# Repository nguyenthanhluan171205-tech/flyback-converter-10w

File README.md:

# flyback-converter-10w
Design, simulation, PCB layout, and experimental validation of a 10W Flyback converter (80-220VAC to 12VDC, 90% efficiency).

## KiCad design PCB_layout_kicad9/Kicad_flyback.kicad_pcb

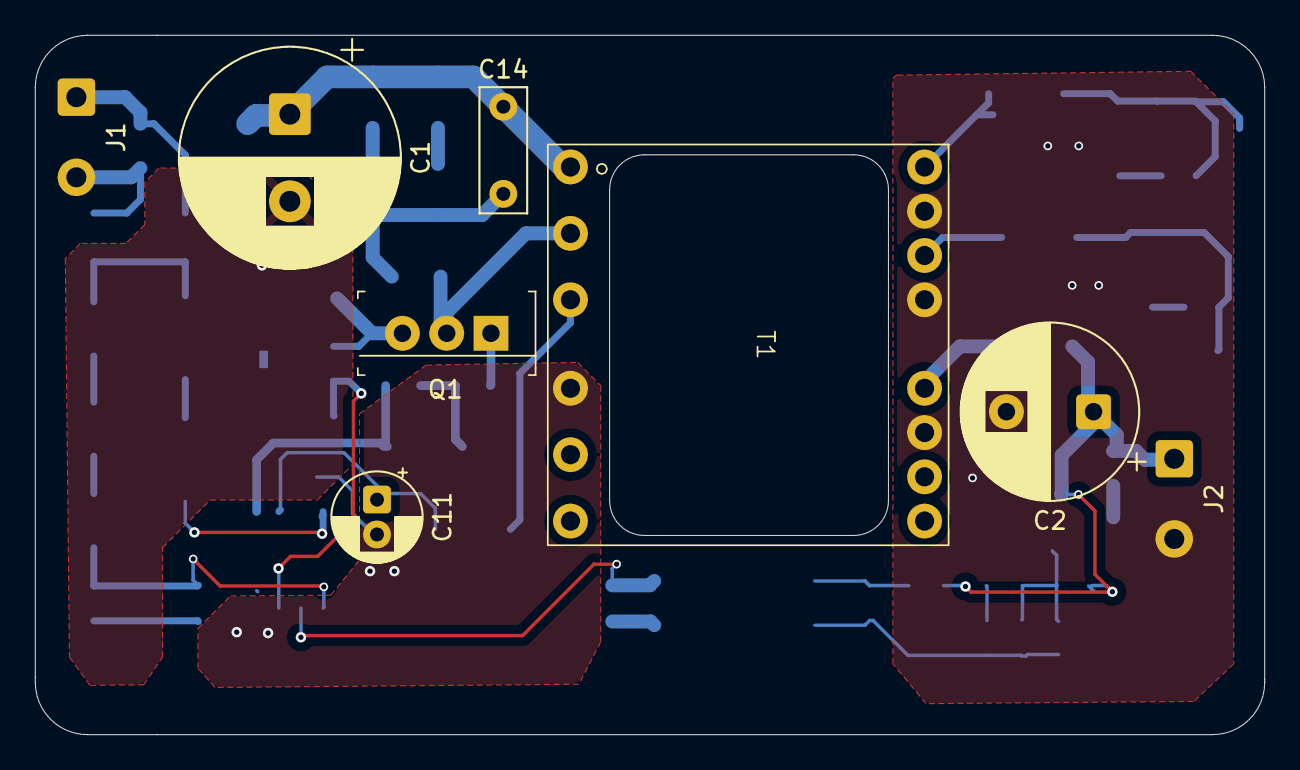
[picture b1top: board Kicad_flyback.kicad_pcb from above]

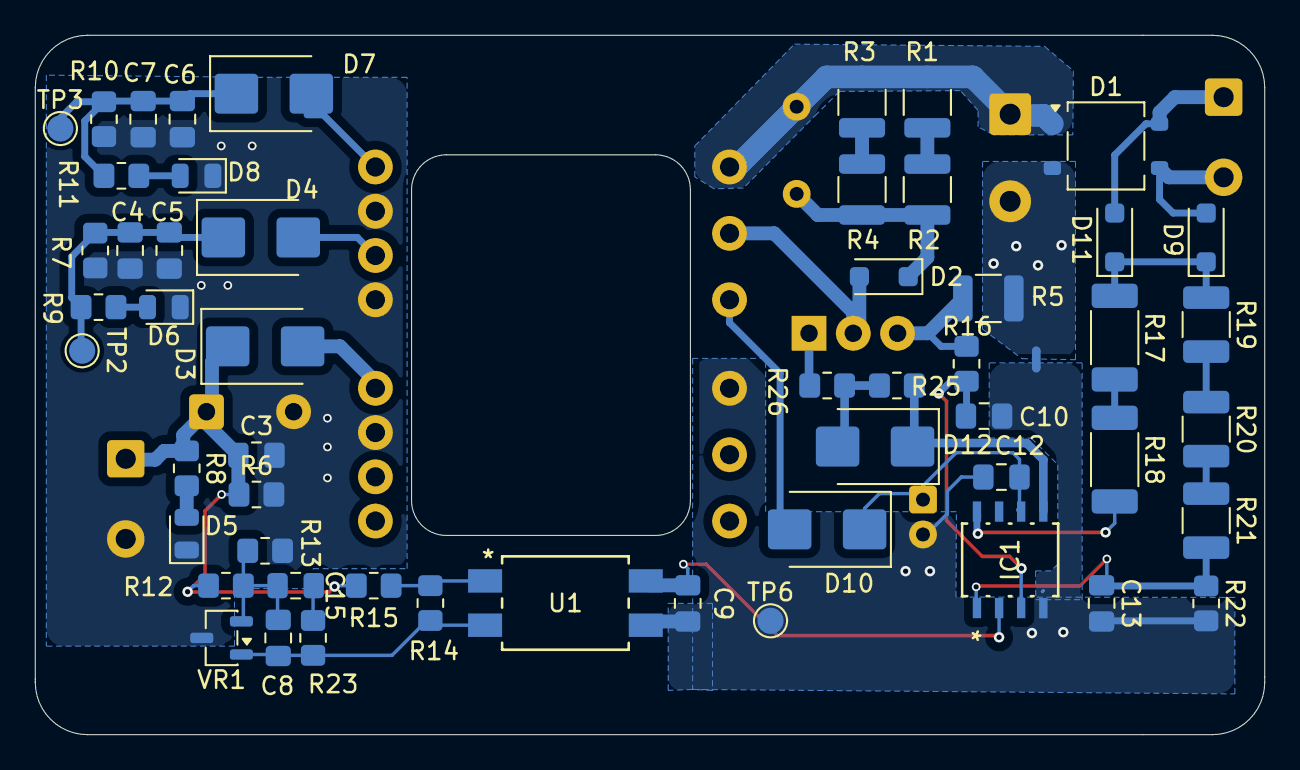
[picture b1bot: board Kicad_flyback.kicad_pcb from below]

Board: 2 copper layers, 70.5 x 40.1 mm, 63 parts (55 on the bottom side), 37 nets.

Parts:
C1: 450V-22uF; CP_Radial_D12.5mm_P5.00mm
C2: 470uF 25V; CP_Radial_D10.0mm_P5.00mm
C3, C4, C5, C6, C7: 106 35V; C_0805_2012Metric_Pad1.18x1.45mm_HandSolder
C8: 22nF; C_0805_2012Metric_Pad1.18x1.45mm_HandSolder
C9: 2.2nF; C_0805_2012Metric_Pad1.18x1.45mm_HandSolder
C10: 101; C_0805_2012Metric_Pad1.18x1.45mm_HandSolder
C11: 10uF 50V; CP_Radial_D5.0mm_P2.00mm
C12: 104 35V; C_0805_2012Metric_Pad1.18x1.45mm_HandSolder
C13: 100pF; C_0805_2012Metric_Pad1.18x1.45mm_HandSolder
C14: 4.7nF; C_Rect_L7.0mm_W2.5mm_P5.00mm
C15: C_0805_2012Metric_Pad1.18x1.45mm_HandSolder
D1: MB6S-TP; TO-269AA
D2, D9, D11: UFM16PL-TP; D_SOD-123F
D3, D4, D7, D10, D12: STPS2200U; D_SMB
D5, D6, D8: LED; LED_0805_2012Metric
IC1: BM1P102FJ-E2; SOP-J8_ROM
J1, J2: Screw_Terminal_01x02; SolderWire-0.5sqmm_1x02_P4.6mm_D0.9mm_OD2.1mm
NT1: NetTie_2; NetTie-2_SMD_Pad0.5mm
Q1: STP2N80K5; TO-220-3
R1, R2, R3, R4: 51k; R_1210_3225Metric
R5: 0.62; R_1210_3225Metric
R6, R7, R8, R9, R10, R11: 10k; R_0805_2012Metric_Pad1.20x1.40mm_HandSolder
R12: 43k; R_0805_2012Metric_Pad1.20x1.40mm_HandSolder
R13: 11k; R_0805_2012Metric_Pad1.20x1.40mm_HandSolder
R14, R16: 1k; R_0805_2012Metric_Pad1.20x1.40mm_HandSolder
R15: 470; R_0805_2012Metric_Pad1.20x1.40mm_HandSolder
R17, R18: 10k 2010; R_2010_5025Metric_Pad1.40x2.65mm_HandSolder
R19, R20, R21: 1.3M 1210; R_1210_3225Metric_Pad1.30x2.65mm_HandSolder
R22: 39k 0805; R_0805_2012Metric_Pad1.20x1.40mm_HandSolder
R23: R_0805_2012Metric_Pad1.20x1.40mm_HandSolder
R25: 150; R_0805_2012Metric_Pad1.20x1.40mm_HandSolder
R26: 22; R_0805_2012Metric_Pad1.20x1.40mm_HandSolder
T1: PQ2016; PQ_2016
TP2, TP3, TP6: TestPoint; TestPoint_Pad_D1.5mm
U1: LTV-817S-TA1-B; LTV-817S_LTO
VR1: TL431BQDBZT; SOT-23-3

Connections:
ACMONI: C13.1, IC1.1 (ACMONI), R21.2, R22.1
AC_1: D1.3 (AC), D9.2 (A), J1.2
AC_2: D1.4 (AC), D11.2 (A), J1.1
FB: C9.2, IC1.2 (FB), U1.4
Gate_drv: D12.1 (K), IC1.5 (OUT), R25.1
HVDC: C1.1, C14.1, D1.1 (+), R1.1, R3.1, T1.1
IC_GND: C9.1, C10.2, C11.2, C12.2, C13.2, IC1.4 (GND), NT1.2, R22.2, T1.4, TP6.1, U1.3
unnamed: C15.1, R23.2
unnamed: D2.2 (A), Q1.2 (D), T1.2
unnamed: C14.2, D2.1 (K), R2.2, R4.2
unnamed: D3.2 (A), T1.11
unnamed: D4.2 (A), T1.9
unnamed: D5.2 (A), R8.2
unnamed: D6.2 (A), R9.2
unnamed: D7.2 (A), T1.7
unnamed: D8.2 (A), R11.2
unnamed: D10.2 (A), T1.3
unnamed: D9.1 (K), D11.1 (K), R17.1, R19.1
unnamed: D12.2 (A), R25.2, R26.1
unnamed: Q1.1 (G), R26.2
unnamed: Q1.3 (S), R5.1, R16.1
unnamed: R1.2, R2.1
unnamed: R3.2, R4.1
unnamed: R14.1, R15.2, U1.1
unnamed: R17.2, R18.1
unnamed: R19.2, R20.1
unnamed: R20.2, R21.1
unnamed: C8.1, R14.2, R23.1, U1.2, VR1.1 (K)
Pri_GND: C1.2, D1.2 (-), NT1.1, R5.2
Sec_GND: C2.2, C3.2, C4.2, C5.2, C6.2, C7.2, D5.1 (K), D6.1 (K), D8.1 (K), J2.2, R6.2, R7.2, R10.2, R13.2, T1.8, T1.10, T1.12, VR1.3 (A)
VCC: C11.1, C12.1, D10.1 (K), IC1.6 (VCC)
VH: IC1.8 (VH), R18.2
Vo_12V: C2.1, C3.1, D3.1 (K), J2.1, R6.1, R8.1, R12.1, R15.1
Vo_15V: C4.1, C5.1, D4.1 (K), R7.1, R9.1, TP2.1
Vo_20V: C6.1, C7.1, D7.1 (K), R10.1, R11.1, TP3.1
Vref_2.495V: C8.2, C15.2, R12.2, R13.1, VR1.2 (REF)
Vsense: C10.1, IC1.3 (CS), R16.2
